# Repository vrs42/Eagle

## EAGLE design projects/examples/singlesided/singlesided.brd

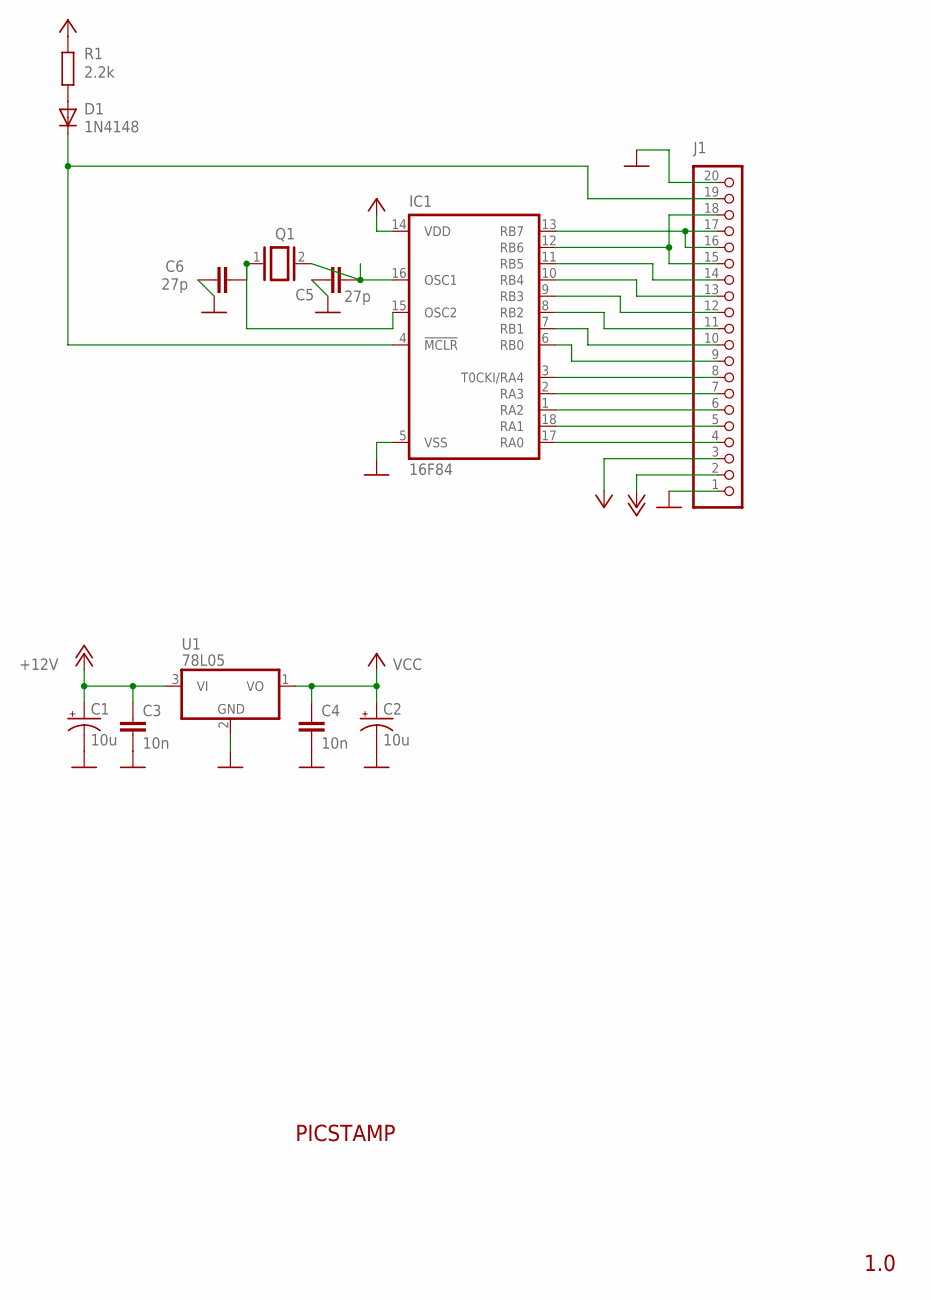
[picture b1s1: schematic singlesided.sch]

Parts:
C1, C2: 10u; E2,5-6
C3, C4: 10n; C025-025X050
C5, C6: 27p; C2.5-2
D1: 1N4148; DO35-10
IC1: 16F84; DIL18
J1: PINHD-1X20; 1X20
Q1: XTAL/S; QS
R1: 2.2k; 0207/10
U1: 78L05; TO92

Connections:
+12V: C1.+, C3.1, J1.2, U1.3 (VI)
A0: IC1.17 (RA0), J1.4
A1: IC1.18 (RA1), J1.5
A2: IC1.1 (RA2), J1.6
A3: IC1.2 (RA3), J1.7
A4: IC1.3 (T0CKI/RA4), J1.8
B0: IC1.6 (RB0), J1.9
B1: IC1.7 (RB1), J1.10
B2: IC1.8 (RB2), J1.11
B3: IC1.9 (RB3), J1.12
B4: IC1.10 (RB4), J1.13
B5: IC1.11 (RB5), J1.14
B6: IC1.12 (RB6), J1.15, J1.18
B7: IC1.13 (RB7), J1.16, J1.17
GND: C1.-, C2.-, C3.2, C4.2, C5.1, C6.1, IC1.5 (VSS), J1.1, J1.20, U1.2 (GND)
unnamed: D1.C, IC1.4 (!MCLR), J1.19
unnamed: D1.A, R1.1
unnamed: C5.2, IC1.16 (OSC1), Q1.2
unnamed: C6.2, IC1.15 (OSC2), Q1.1
VCC: C2.+, C4.1, IC1.14 (VDD), J1.3, R1.2, U1.1 (VO)

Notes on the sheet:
PICSTAMP
1.0

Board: 2 copper layers, 12 parts (0 on the bottom side), 20 nets, no tracks yet.

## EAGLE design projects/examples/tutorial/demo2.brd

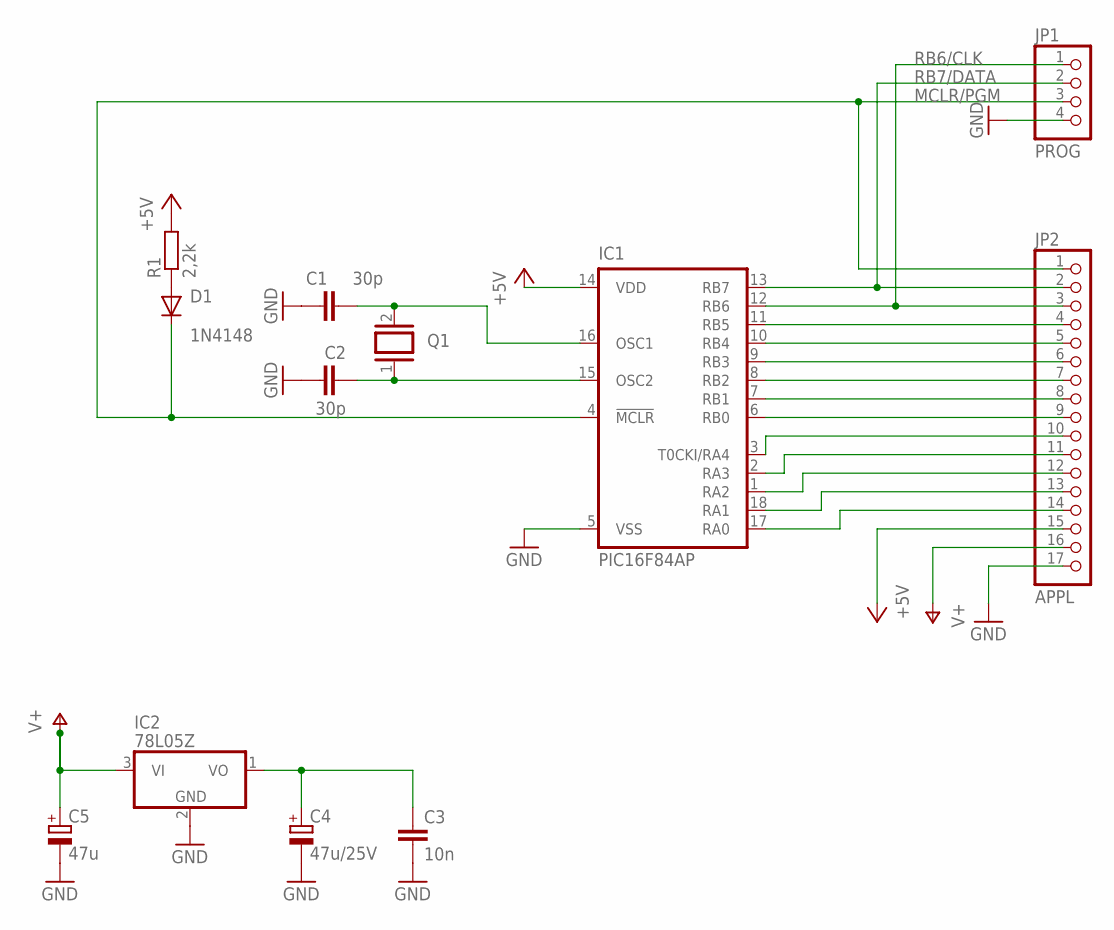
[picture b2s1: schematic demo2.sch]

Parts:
C1, C2: 30p; C1206
C3: 10n; C025-025X050
C4: 47u/25V; TAP5-45
C5: 47u; TAP5-45
D1: 1N4148; DO35-10
IC1: PIC16F84AP; DIL18
IC2: 78L05Z; TO92
JP1: PROG; 1X04
JP2: APPL; 1X17
Q1: XTAL/S; QS
R1: 2,2k; R1206

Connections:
+5V: IC1.14 (VDD), JP2.15, R1.2
GND: C1.1, C2.1, C3.2, C4.-, C5.-, IC1.5 (VSS), IC2.2 (GND), JP1.4, JP2.17
MCLR/PGM: D1.C, IC1.4 (!MCLR), JP1.3, JP2.1
unnamed: C3.1, C4.+, IC2.1 (VO)
unnamed: C1.2, IC1.16 (OSC1), Q1.2
unnamed: C2.2, IC1.15 (OSC2), Q1.1
unnamed: D1.A, R1.1
RA0: IC1.17 (RA0), JP2.14
RA1: IC1.18 (RA1), JP2.13
RA2: IC1.1 (RA2), JP2.12
RA3: IC1.2 (RA3), JP2.11
RA4: IC1.3 (T0CKI/RA4), JP2.10
RB0: IC1.6 (RB0), JP2.9
RB1: IC1.7 (RB1), JP2.8
RB2: IC1.8 (RB2), JP2.7
RB3: IC1.9 (RB3), JP2.6
RB4: IC1.10 (RB4), JP2.5
RB5: IC1.11 (RB5), JP2.4
RB6/CLK: IC1.12 (RB6), JP1.1, JP2.3
RB7/DATA: IC1.13 (RB7), JP1.2, JP2.2
V+: C5.+, IC2.3 (VI), JP2.16

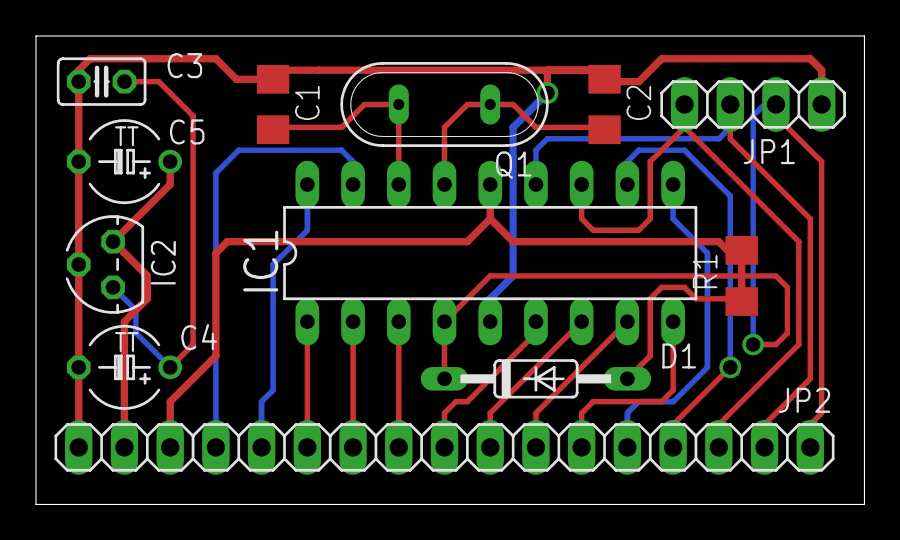
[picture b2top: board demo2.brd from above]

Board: 2 copper layers, 46.0 x 26.0 mm, 12 parts (0 on the bottom side), 21 nets.

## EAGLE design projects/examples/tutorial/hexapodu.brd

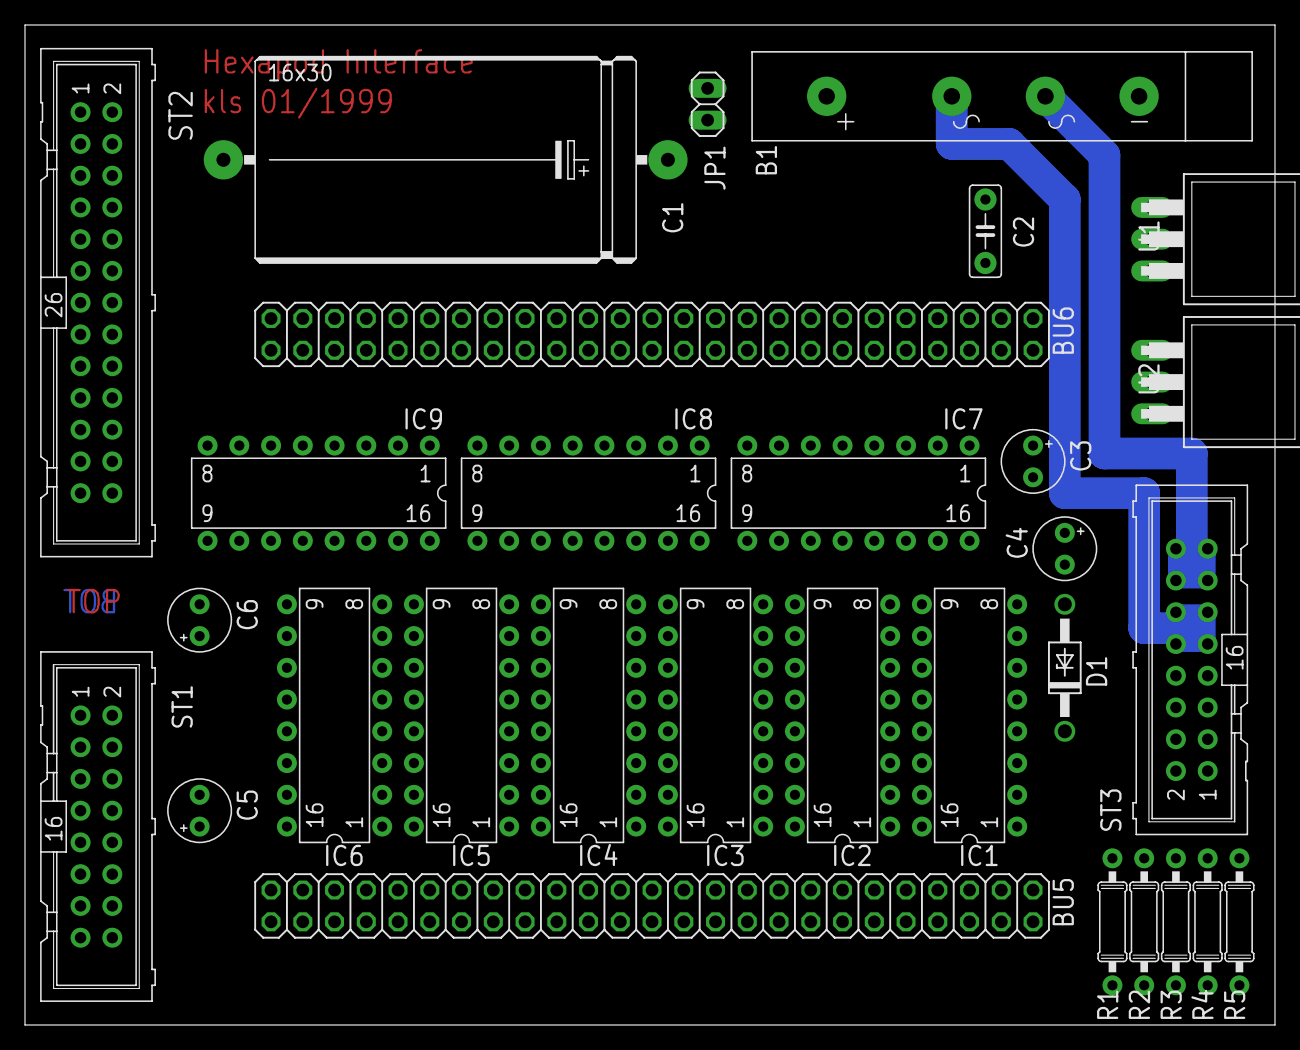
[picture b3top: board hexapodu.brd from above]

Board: 2 copper layers, 100.0 x 80.0 mm, 30 parts (0 on the bottom side), 68 nets.

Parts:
B1: FB100
BU5, BU6: PINHD-2X25; 2X25
C1: 2200uF/35V; E35-16
C2: 100nf; C5B2,5A
C3, C6: 4,7uf/35V; E2,5-5
C4, C5: 4,7uf/10V; E2,5-5
D1: BZX85; DO41Z10
IC1, IC2, IC3, IC4, IC5, IC6: HCTL2016; DIL-16
IC7, IC8, IC9: DS3668; DIL-16
JP1: PINHD-1X2; 1X02
R1, R2, R4, R5: 0207/10
R3: 10k; 0207/10@1
ST1, ST3: PINHD-2X8; ML16
ST2: PINHD-2X13; ML26
U1: 78S24; TO220H
U2: 7805; TO220H

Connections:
!OE0: BU6.5, IC1.4
!OE1: BU6.8, IC2.4
!OE2: BU6.7, IC3.4
!OE3: BU6.10, IC4.4
!OE4: BU6.9, IC5.4
!OE5: BU6.12, IC6.4
!RST: BU6.14, IC1.5, IC2.5, IC3.5, IC4.5, IC5.5, IC6.5
+5V: BU6.50, C4.+, C5.+, D1.C, IC1.16, IC2.16, IC3.16, IC4.16, IC5.16, IC6.16, IC7.11, IC8.11, IC9.11, R1.1, R2.1, R4.1, ST1.3, ST1.4, U2.3
+24V: C3.+, C6.+, IC7.2, IC7.7, IC8.2, IC8.7, IC9.2, IC9.7, R5.1, ST2.1, ST2.3, ST2.5, ST2.7, ST2.9, ST2.11, ST2.13, ST2.15, ST2.17, ST2.19, ST2.21, ST2.23, ST2.25, ST2.26, U1.3
AC1: B1.AC1, ST3.9, ST3.10, ST3.11, ST3.12
AC2: B1.AC2, ST3.13, ST3.14, ST3.15, ST3.16
CLK: BU6.1, IC1.2, IC2.2, IC3.2, IC4.2, IC5.2, IC6.2
COIL0: IC7.1, ST2.2
COIL1: IC7.3, ST2.4
COIL2: IC7.6, ST2.6
COIL3: IC7.8, ST2.8
COIL4: IC8.1, ST2.10
COIL5: IC8.3, ST2.12
COIL6: IC8.6, ST2.14
COIL7: IC8.8, ST2.16
COIL8: IC9.1, ST2.18
COIL9: IC9.3, ST2.20
COIL10: IC9.6, ST2.22
COIL11: IC9.8, ST2.24
D0: BU6.13, IC1.1, IC2.1, IC3.1, IC4.1, IC5.1, IC6.1
D1: BU6.16, IC1.15, IC2.15, IC3.15, IC4.15, IC5.15, IC6.15
D2: BU6.15, IC1.14, IC2.14, IC3.14, IC4.14, IC5.14, IC6.14
D3: BU6.18, IC1.13, IC2.13, IC3.13, IC4.13, IC5.13, IC6.13
D4: BU6.17, IC1.12, IC2.12, IC3.12, IC4.12, IC5.12, IC6.12
D5: BU6.20, IC1.11, IC2.11, IC3.11, IC4.11, IC5.11, IC6.11
D6: BU6.19, IC1.10, IC2.10, IC3.10, IC4.10, IC5.10, IC6.10
D7: BU6.22, IC1.9, IC2.9, IC3.9, IC4.9, IC5.9, IC6.9
EN: BU5.9, IC7.14, IC8.14, IC9.14, R3.2
ENC0: IC1.7, ST1.5
ENC1: IC1.6, ST1.6
ENC2: IC2.7, ST1.7
ENC3: IC2.6, ST1.8
ENC4: IC3.7, ST1.9
ENC5: IC3.6, ST1.10
ENC6: IC4.7, ST1.11
ENC7: IC4.6, ST1.12
ENC8: IC5.7, ST1.13
ENC9: IC5.6, ST1.14
ENC10: IC6.7, ST1.15
ENC11: IC6.6, ST1.16
GND: B1.-, BU6.49, C1.-, C2.1, C3.-, C4.-, C5.-, C6.-, D1.A, IC1.8, IC2.8, IC3.8, IC4.8, IC5.8, IC6.8, IC7.4, IC7.5, IC7.12, IC7.13, IC8.4, IC8.5, IC8.12, IC8.13, IC9.4, IC9.5, IC9.12, IC9.13, R3.1, ST1.1, ST1.2, ST3.2, ST3.4, U1.2, U2.2
unnamed: R5.2, ST3.1
unnamed: R4.2, ST3.3
unnamed: R2.2, ST3.5
unnamed: R1.2, ST3.7
unnamed: BU6.35, JP1.2
unnamed: BU6.37, JP1.1
SEL: BU6.11, IC1.3, IC2.3, IC3.3, IC4.3, IC5.3, IC6.3
STATUS0: BU5.7, ST3.8
STATUS1: BU5.6, ST3.6
VALVE0: BU5.21, IC7.16
VALVE1: BU5.20, IC7.15
VALVE2: BU5.19, IC7.10
VALVE3: BU5.18, IC7.9
VALVE4: BU5.17, IC8.16
VALVE5: BU5.16, IC8.15
VALVE6: BU5.15, IC8.10
VALVE7: BU5.14, IC8.9
VALVE8: BU5.13, IC9.16
VALVE9: BU5.12, IC9.15
VALVE10: BU5.11, IC9.10
VALVE11: BU5.10, IC9.9
VIN: B1.+, C1.+, C2.2, U1.1, U2.1

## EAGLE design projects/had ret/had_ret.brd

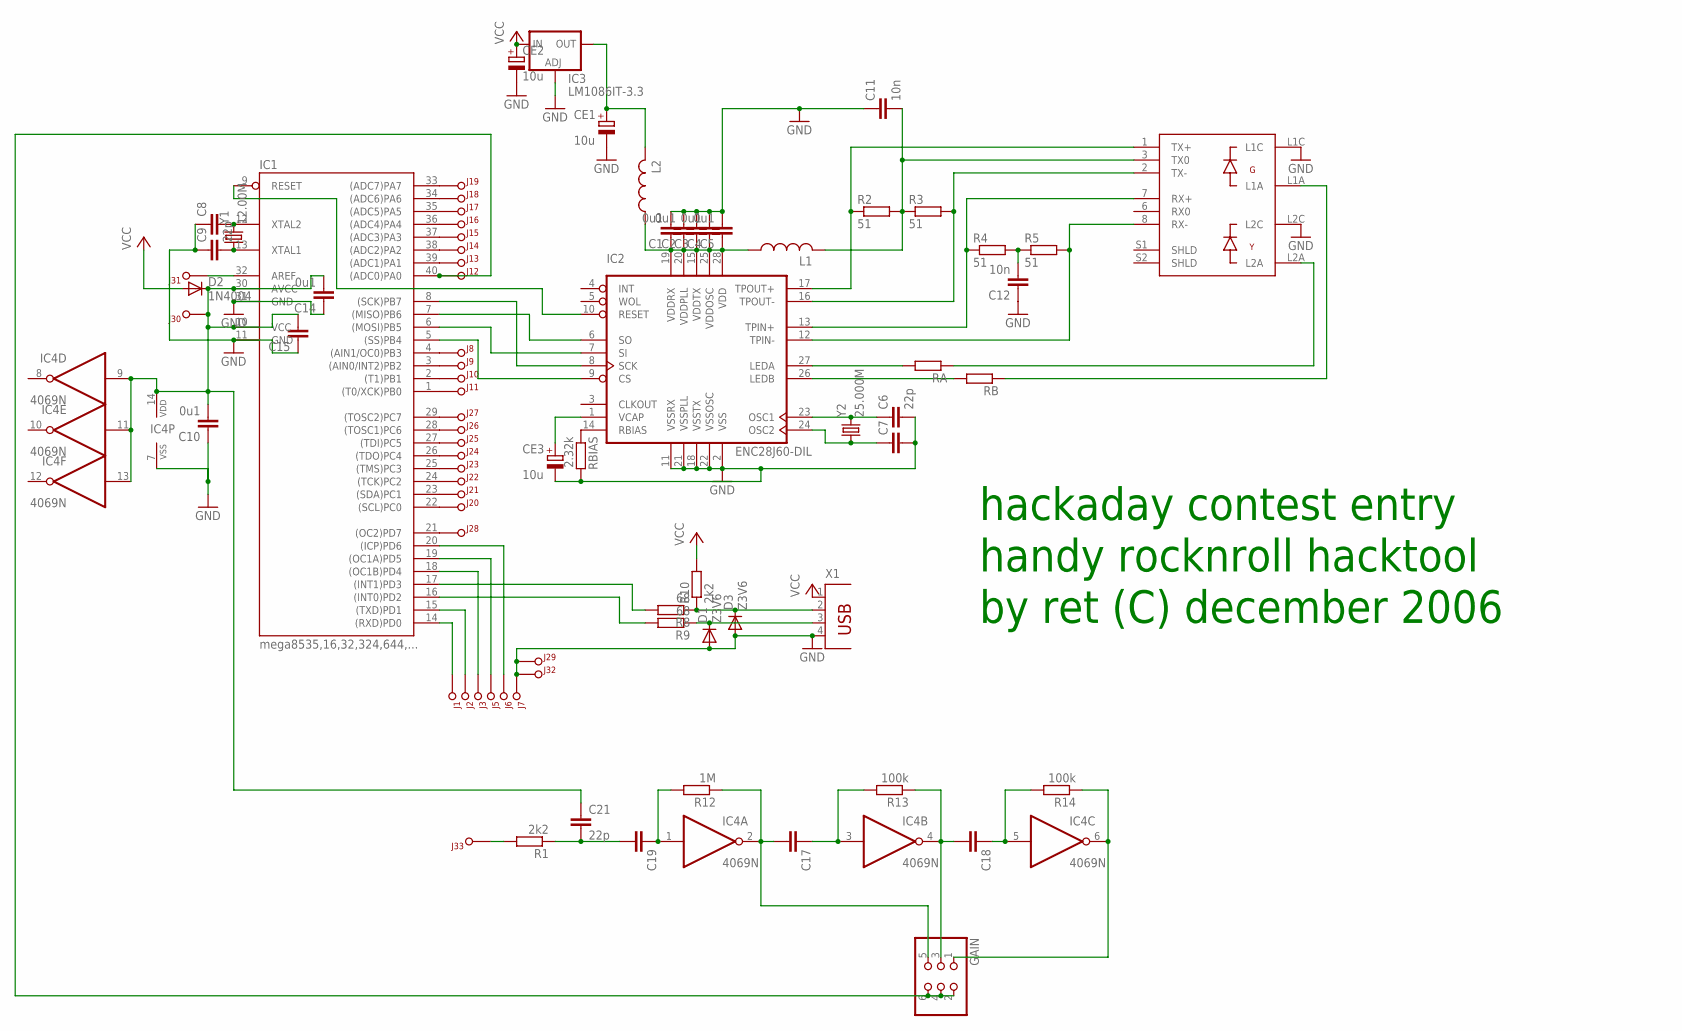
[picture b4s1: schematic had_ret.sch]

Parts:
C1, C2, C4, C5, C10, C14: 0u1; 0805
C3, C7, C8, C15, C17, C18, C19: C0805; 0805
C6, C9, C21: 22p; 0805
C11, C12: 10n; 0805
CE1, CE2, CE3: 10u; CT3528
D1, D3: Z3V6; DIODE
D2: 1N4004; DO41-10
GAIN: PINHD-2X3; 2X03
IC1: mega8535,16,32,324,644,...; DIL40
IC2: ENC28J60-DIL; DIL28-3
IC3: LM1086IT-3.3; 317TS
IC4: 4069N; DIL14
J1, J2, J3, J5, J6, J7, J8, J9, J10, J11, J12, J13, J14, J15, J16, J17, J18, J19, J20, J21, J22, J23, J24, J25, J26, J27, J28, J29, J30, J31, J32, J33: PINMA01; MA01-1PIN
J4: 8P8C-TRAF
L1, L2: L0805; 0805
R1, R10: 2k2; 0805
R2, R3, R4, R5: 51; 0805
R8, R9: 68; 0805
R12: 1M; 0805
R13, R14: 100k; 0805
RA: R-EU_0204/5; 0204/5
RB: R-EU_0204/5; 0204/5
RBIAS: 2.32k; 0204/7
X1: PN61729
Y1: 12.00M; HC49/S
Y2: 25.000M; HC49/S

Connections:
+3V3: CE1.+, IC3.2 (OUT), L2.2
GND: C1.2, C2.2, C3.2, C4.2, C5.2, C6.2, C7.2, C8.1, C9.1, C10.1, C11.1, C12.1, C14.1, C15.1, CE1.-, CE2.-, CE3.-, D1.A, D3.A, IC1.11 (GND), IC1.31 (GND), IC2.2 (VSS), IC2.11 (VSSRX), IC2.18 (VSSTX), IC2.21 (VSSPLL), IC2.22 (VSSOSC), IC3.1 (ADJ), IC4.7 (VSS), J4.L1C, J4.L2C, J7.1, J29.1, J32.1, RBIAS.2, X1.4
MISO: IC1.7 ((MISO)PB6), IC2.6 (SO)
MOSI: IC1.6 ((MOSI)PB5), IC2.7 (SI)
unnamed: IC1.15 ((TXD)PD1), J2.1
unnamed: IC1.14 ((RXD)PD0), J1.1
unnamed: CE3.+, IC2.1 (VCAP)
unnamed: IC1.17 ((INT1)PD3), R8.2
unnamed: IC1.16 ((INT0)PD2), R9.2
unnamed: C1.1, C2.1, C3.1, C4.1, C5.1, IC2.15 (VDDTX), IC2.19 (VDDRX), IC2.20 (VDDPLL), IC2.25 (VDDOSC), IC2.28 (VDD), L1.1, L2.1
unnamed: IC1.32 (AREF), J31.1
unnamed: IC2.26 (LEDB), RB.2
unnamed: IC2.27 (LEDA), RA.2
unnamed: IC1.18 ((OC1B)PD4), J3.1
unnamed: J4.L2A, RA.1
unnamed: IC2.16 (TPOUT-), J4.2 (TX-), R3.2
unnamed: IC2.12 (TPIN-), J4.8 (RX-), R5.2
unnamed: IC2.13 (TPIN+), J4.7 (RX+), R4.1
unnamed: C11.2, J4.3 (TX0), L1.2, R2.2, R3.1
unnamed: C8.2, IC1.12 (XTAL2), Y1.2
unnamed: C9.2, IC1.13 (XTAL1), Y1.1
unnamed: C6.1, IC2.23 (OSC1), Y2.2
unnamed: C7.1, IC2.24 (OSC2), Y2.1
unnamed: IC2.17 (TPOUT+), J4.1 (TX+), R2.1
unnamed: J4.L1A, RB.1
unnamed: IC2.14 (RBIAS), RBIAS.1
unnamed: IC1.19 ((OC1A)PD5), J5.1
unnamed: IC1.20 ((ICP)PD6), J6.1
unnamed: D3.K (C), R8.1, R10.1, X1.2
unnamed: D1.K (C), R9.1, X1.3
unnamed: IC1.4 ((AIN1/OC0)PB3), J8.1
unnamed: IC1.3 ((AIN0/INT2)PB2), J9.1
unnamed: IC1.2 ((T1)PB1), J10.1
unnamed: IC1.1 ((T0/XCK)PB0), J11.1
unnamed: GAIN.2, GAIN.4, GAIN.6, IC1.40 ((ADC0)PA0), J12.1
unnamed: IC1.39 ((ADC1)PA1), J13.1
unnamed: IC1.38 ((ADC2)PA2), J14.1
unnamed: IC1.37 ((ADC3)PA3), J15.1
unnamed: IC1.36 ((ADC4)PA4), J16.1
unnamed: IC1.35 ((ADC5)PA5), J17.1
unnamed: IC1.34 ((ADC6)PA6), J18.1
unnamed: IC1.33 ((ADC7)PA7), J19.1
unnamed: IC1.22 ((SCL)PC0), J20.1
unnamed: IC1.23 ((SDA)PC1), J21.1
unnamed: IC1.24 ((TCK)PC2), J22.1
unnamed: IC1.25 ((TMS)PC3), J23.1
unnamed: IC1.26 ((TDO)PC4), J24.1
unnamed: IC1.27 ((TDI)PC5), J25.1
unnamed: IC1.28 ((TOSC1)PC6), J26.1
unnamed: IC1.29 ((TOSC2)PC7), J27.1
unnamed: IC1.21 ((OC2)PD7), J28.1
unnamed: C12.2, R4.2, R5.1
unnamed: C19.1, IC4.1 (I), R12.2
unnamed: C17.2, GAIN.5, IC4.2 (O), R12.1
unnamed: C17.1, IC4.3 (I), R13.2
unnamed: C18.2, GAIN.3, IC4.4 (O), R13.1
unnamed: J33.1, R1.2
unnamed: C19.2, C21.2, R1.1
unnamed: C18.1, IC4.5 (I), R14.2
unnamed: GAIN.1, IC4.6 (O), R14.1
RST: IC1.9 (RESET), IC2.10 (RESET)
SCK: IC1.8 ((SCK)PB7), IC2.8 (SCK)
SS: IC1.5 ((SS)PB4), IC2.9 (CS)
V4.4: C10.2, C14.2, C15.2, C21.1, D2.C, IC1.10 (VCC), IC1.30 (AVCC), IC4.9 (I), IC4.11 (I), IC4.13 (I), IC4.14 (VDD), J30.1
VCC: CE2.+, D2.A, IC3.3 (IN), R10.2, X1.1

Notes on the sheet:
hackaday contest entry
handy rocknroll hacktool
by ret (C) december 2006

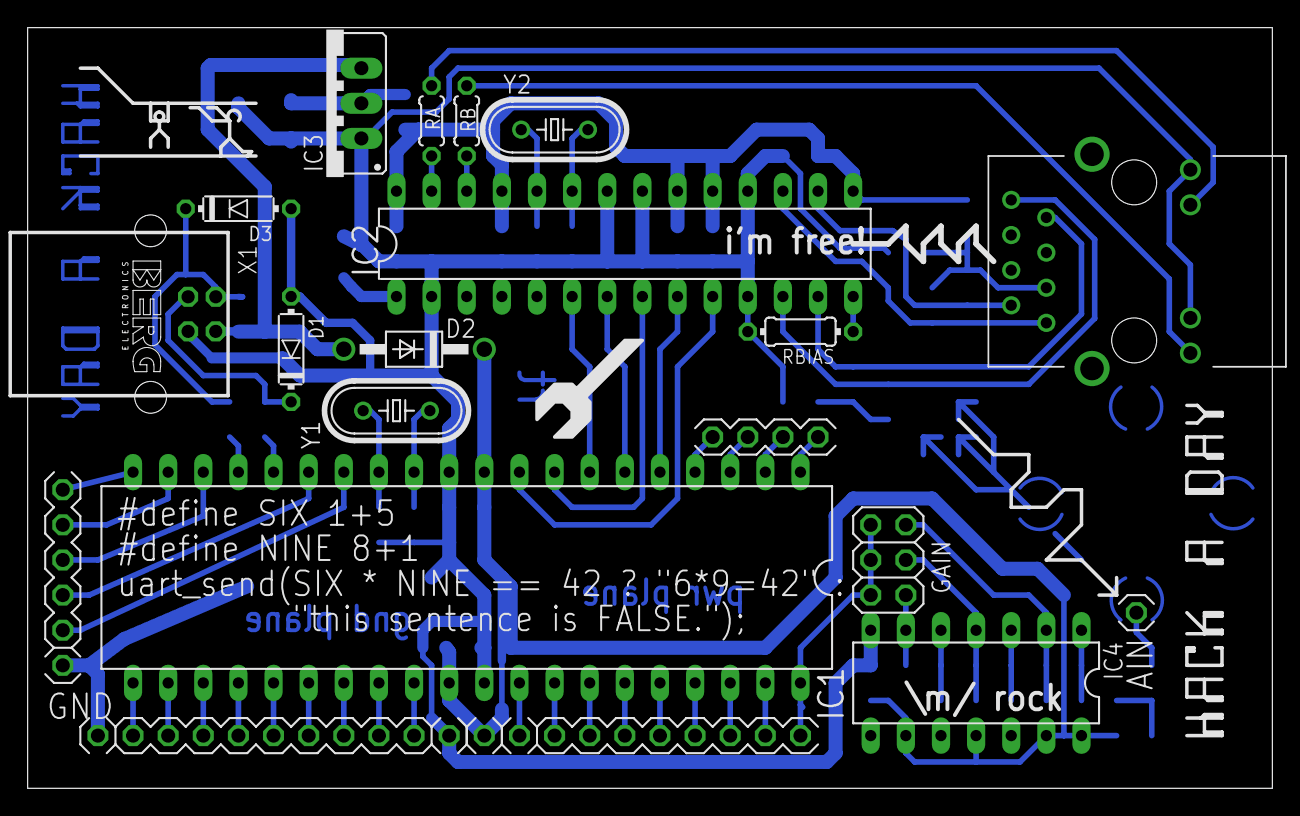
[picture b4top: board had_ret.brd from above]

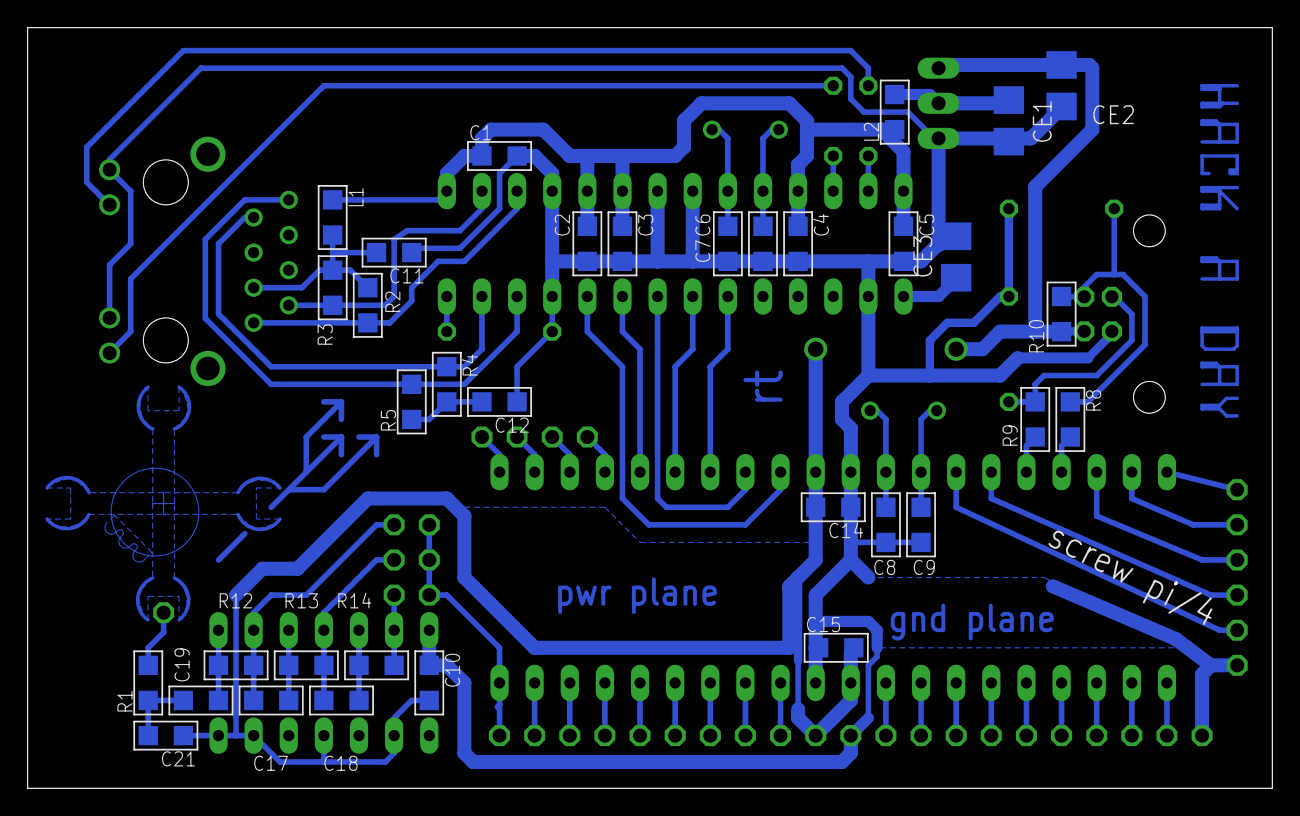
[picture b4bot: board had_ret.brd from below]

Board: 2 copper layers, 90.0 x 55.0 mm, 81 parts (34 on the bottom side), 65 nets.

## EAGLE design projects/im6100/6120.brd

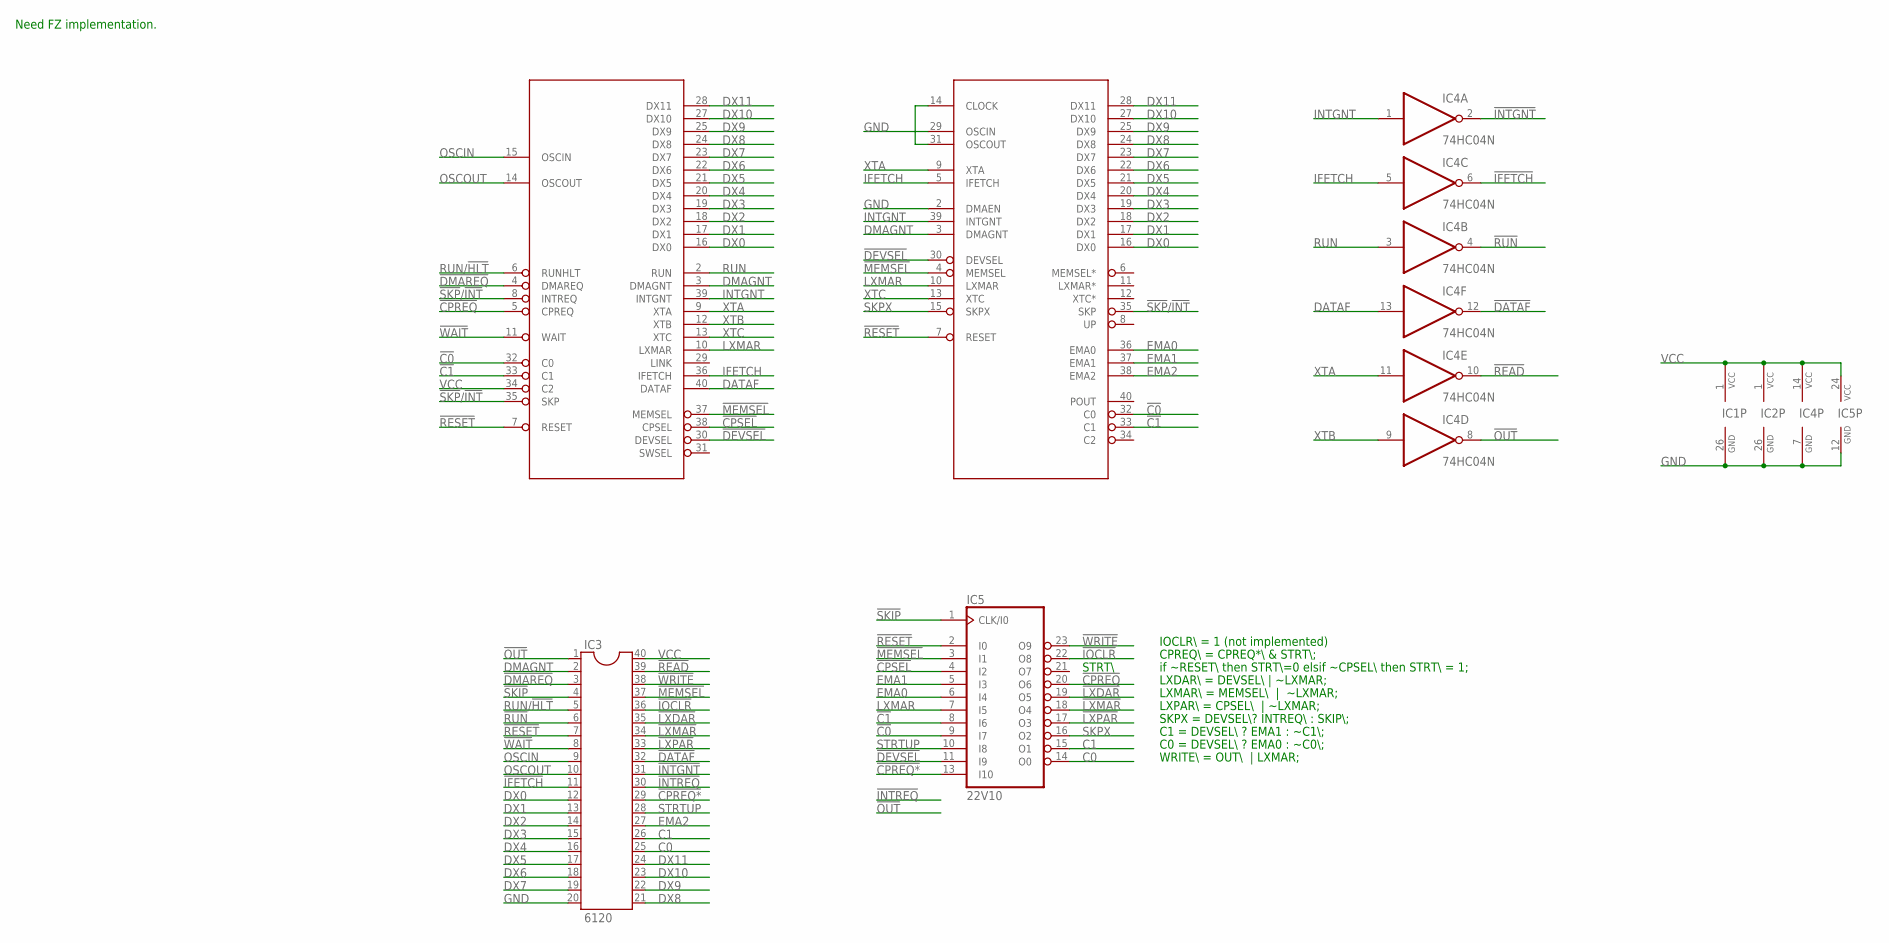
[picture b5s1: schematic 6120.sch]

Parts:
IC1: IM6100; DIL40
IC2: IM6102; DIL40
IC3: 6120; DIL40
IC4: 74HC04N; DIL14
IC5: 22V10; DIL24-3

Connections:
!C0: IC1.32 (C0), IC2.32 (C0), IC5.9 (I7)
!C1: IC1.33 (C1), IC2.33 (C1), IC5.8 (I6)
!CPREQ: IC1.5 (CPREQ), IC5.20 (O6)
!CPREQ*: IC3.29, IC5.13 (I10)
!CPSEL: IC1.38 (CPSEL), IC5.4 (I2)
!DATAF: IC3.32, IC4.12 (O)
!DEVSEL: IC1.30 (DEVSEL), IC2.30 (DEVSEL), IC5.11 (I9)
!DMAREQ: IC1.4 (DMAREQ), IC3.3
!IFETCH: IC3.11, IC4.6 (O)
!INTGNT: IC3.31, IC4.2 (O)
!INTREQ: IC3.30
!IOCLR: IC3.36, IC5.22 (O8)
!LXDAR: IC3.35, IC5.19 (O5)
!LXMAR: IC3.34, IC5.18 (O4)
!LXPAR: IC3.33, IC5.17 (O3)
!MEMSEL: IC1.37 (MEMSEL), IC2.4 (MEMSEL), IC3.37, IC5.3 (I1)
!OUT: IC3.1, IC4.8 (O)
!READ: IC3.39, IC4.10 (O)
!RESET: IC1.7 (RESET), IC2.7 (RESET), IC3.7, IC5.2 (I0)
!RUN: IC3.6, IC4.4 (O)
!SKIP: IC3.4, IC5.1 (CLK/I0)
!SKP!/!INT: IC1.8 (INTREQ), IC1.35 (SKP), IC2.35 (SKP)
!WAIT: IC1.11 (WAIT), IC3.8
!WRITE: IC3.38, IC5.23 (O9)
C0: IC3.25, IC5.14 (O0)
C1: IC3.26, IC5.15 (O1)
DATAF: IC1.40 (DATAF), IC4.13 (I)
DMAGNT: IC1.3 (DMAGNT), IC2.3 (DMAGNT), IC3.2
DX0: IC1.16 (DX0), IC2.16 (DX0), IC3.12
DX1: IC1.17 (DX1), IC2.17 (DX1), IC3.13
DX2: IC1.18 (DX2), IC2.18 (DX2), IC3.14
DX3: IC1.19 (DX3), IC2.19 (DX3), IC3.15
DX4: IC1.20 (DX4), IC2.20 (DX4), IC3.16
DX5: IC1.21 (DX5), IC2.21 (DX5), IC3.17
DX6: IC1.22 (DX6), IC2.22 (DX6), IC3.18
DX7: IC1.23 (DX7), IC2.23 (DX7), IC3.19
DX8: IC1.24 (DX8), IC2.24 (DX8), IC3.21
DX9: IC1.25 (DX9), IC2.25 (DX9), IC3.22
DX10: IC1.27 (DX10), IC2.27 (DX10), IC3.23
DX11: IC1.28 (DX11), IC2.28 (DX11), IC3.24
EMA0: IC2.36 (EMA0), IC5.6 (I4)
EMA1: IC2.37 (EMA1), IC5.5 (I3)
EMA2: IC2.38 (EMA2), IC3.27
GND: IC1.26 (GND), IC2.2 (DMAEN), IC2.26 (GND), IC2.29 (OSCIN), IC3.20, IC4.7 (GND), IC5.12 (GND)
IFETCH: IC1.36 (IFETCH), IC2.5 (IFETCH), IC4.5 (I)
INTGNT: IC1.39 (INTGNT), IC2.39 (INTGNT), IC4.1 (I)
LXMAR: IC1.10 (LXMAR), IC2.10 (LXMAR), IC5.7 (I5)
unnamed: IC2.14 (CLOCK), IC2.31 (OSCOUT)
OSCIN: IC1.15 (OSCIN), IC3.9
OSCOUT: IC1.14 (OSCOUT), IC3.10
RUN: IC1.2 (RUN), IC4.3 (I)
RUN/!HLT: IC1.6 (RUNHLT), IC3.5
SKPX: IC2.15 (SKPX), IC5.16 (O2)
STRTUP: IC3.28, IC5.10 (I8)
VCC: IC1.1 (VCC), IC1.34 (C2), IC2.1 (VCC), IC3.40, IC4.14 (VCC), IC5.24 (VCC)
XTA: IC1.9 (XTA), IC2.9 (XTA), IC4.11 (I)
XTB: IC1.12 (XTB), IC4.9 (I)
XTC: IC1.13 (XTC), IC2.13 (XTC)

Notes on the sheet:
Need FZ implementation.
C0 = DEVSEL\\ ? EMA0 : ~C0\\;
C1 = DEVSEL\\ ? EMA1 : ~C1\\;
LXPAR\\ = CPSEL\\ | ~LXMAR;
LXMAR\\ = MEMSEL\\ | ~LXMAR;
CPREQ\\ = CPREQ*\\ & STRT\\;
LXDAR\\ = DEVSEL\\ | ~LXMAR;
SKPX = DEVSEL\\? INTREQ\\ : SKIP\\;
WRITE\\ = OUT\\ | LXMAR;
IOCLR\\ = 1 (not implemented)
if ~RESET\\ then STRT\\=0 elsif ~CPSEL\\ then STRT\\ = 1;
STRT\\

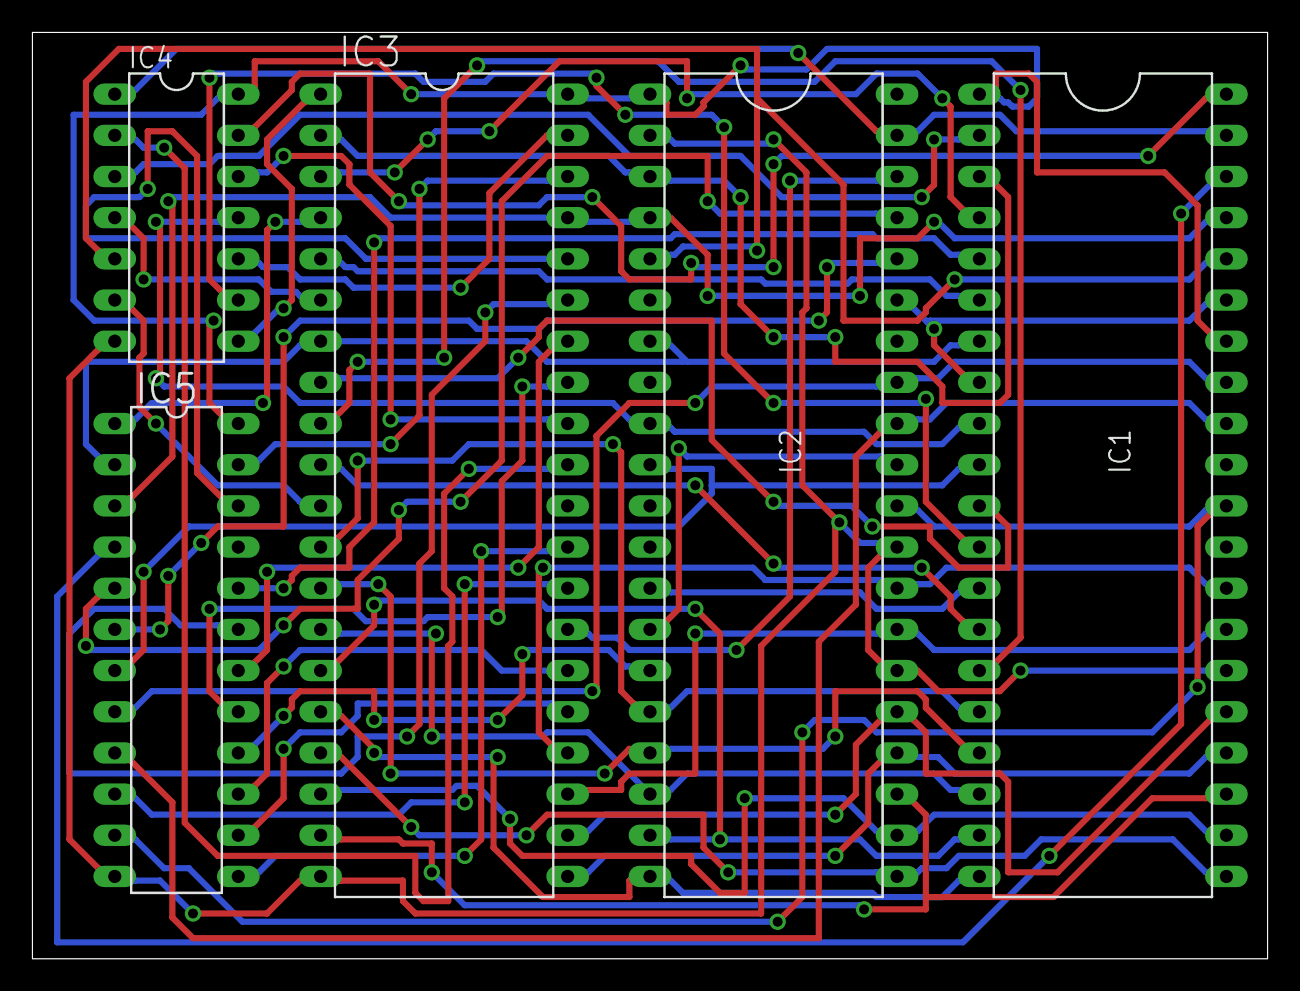
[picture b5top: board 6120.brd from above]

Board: 2 copper layers, 76.2 x 57.1 mm, 5 parts (0 on the bottom side), 57 nets.

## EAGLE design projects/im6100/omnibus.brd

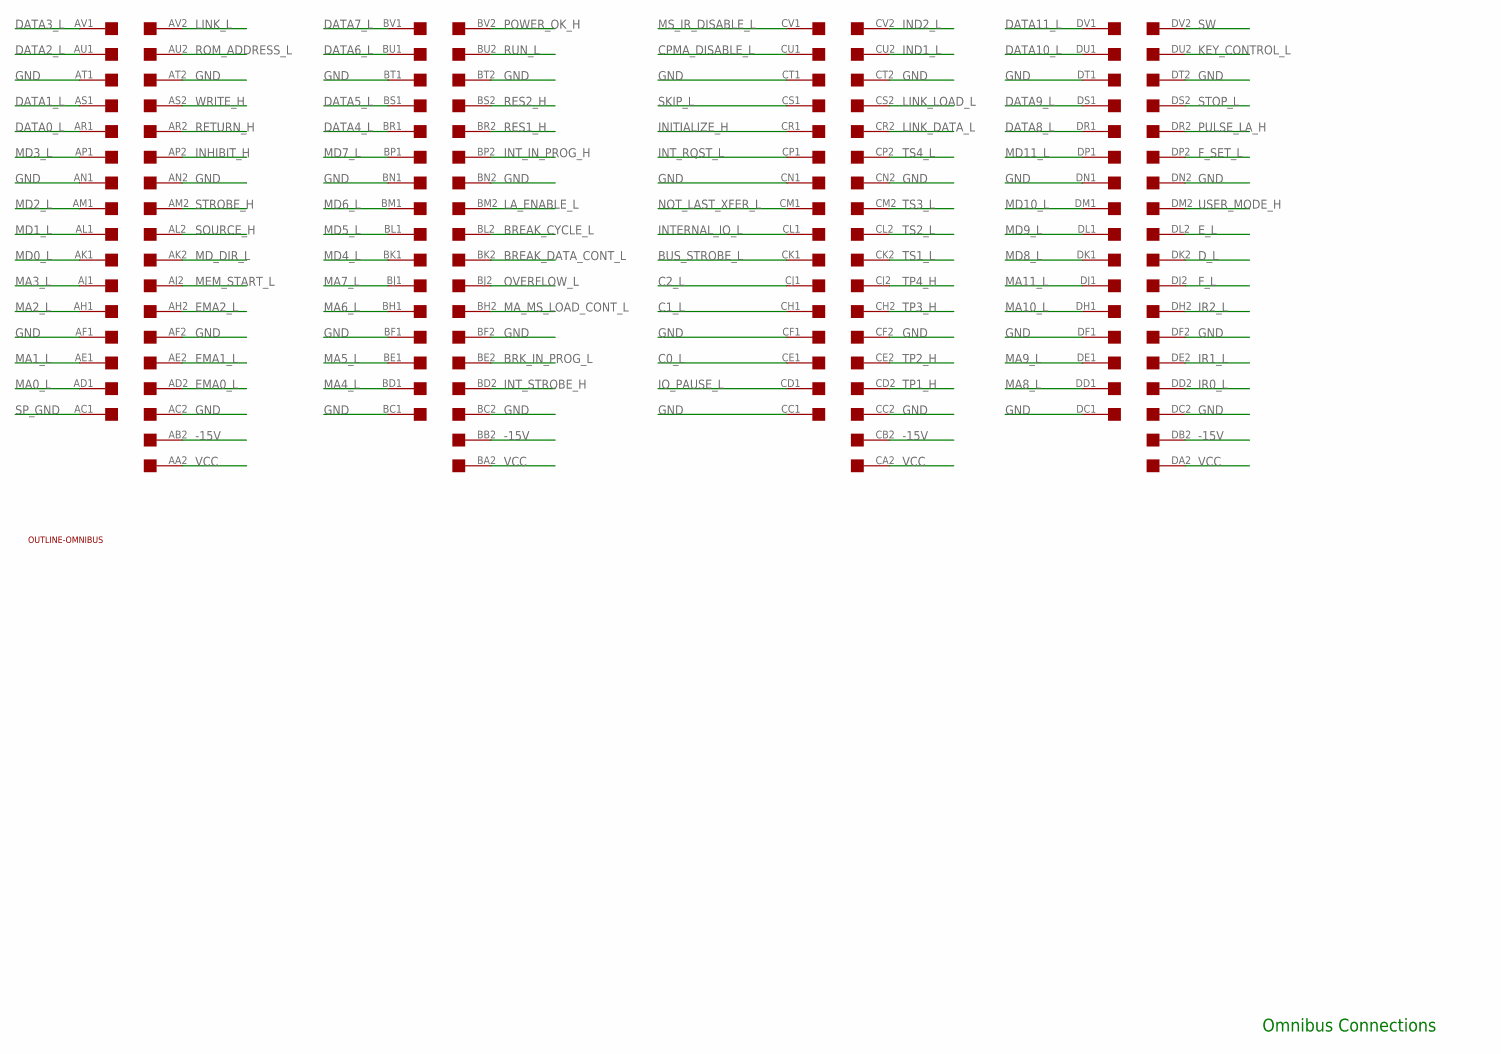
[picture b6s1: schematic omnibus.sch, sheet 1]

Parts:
U$1: OUTLINE-OMNIBUS; OMNIBUS
U$2: QUAD; EDGE-CON8

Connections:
-15V: U$2.AB2, U$2.BB2, U$2.CB2, U$2.DB2
BREAK_CYCLE_L: U$2.BL2
BREAK_DATA_CONT_L: U$2.BK2
BRK_IN_PROG_L: U$2.BE2
BUS_STROBE_L: U$2.CK1
C0_L: U$2.CE1; also elsewhere on the board
C1_L: U$2.CH1; also elsewhere on the board
C2_L: U$2.CJ1
CPMA_DISABLE_L: U$2.CU1
DATA0_L: U$2.AR1; also elsewhere on the board
DATA1_L: U$2.AS1; also elsewhere on the board
DATA2_L: U$2.AU1; also elsewhere on the board
DATA3_L: U$2.AV1; also elsewhere on the board
DATA4_L: U$2.BR1; also elsewhere on the board
DATA5_L: U$2.BS1; also elsewhere on the board
DATA6_L: U$2.BU1; also elsewhere on the board
DATA7_L: U$2.BV1; also elsewhere on the board
DATA8_L: U$2.DR1; also elsewhere on the board
DATA9_L: U$2.DS1; also elsewhere on the board
DATA10_L: U$2.DU1; also elsewhere on the board
DATA11_L: U$2.DV1; also elsewhere on the board
D_L: U$2.DK2
EMA0_L: U$2.AD2; also elsewhere on the board
EMA1_L: U$2.AE2; also elsewhere on the board
EMA2_L: U$2.AH2; also elsewhere on the board
E_L: U$2.DL2
F_L: U$2.DJ2
F_SET_L: U$2.DP2
GND: U$2.AC2, U$2.AF1, U$2.AF2, U$2.AN1, U$2.AN2, U$2.AT1, U$2.AT2, U$2.BC1, U$2.BC2, U$2.BF1, U$2.BF2, U$2.BN1, U$2.BN2, U$2.BT1, U$2.BT2, U$2.CC1, U$2.CC2, U$2.CF1, U$2.CF2, U$2.CN1, U$2.CN2, U$2.CT1, U$2.CT2, U$2.DC1, U$2.DC2, U$2.DF1, U$2.DF2, U$2.DN1, U$2.DN2, U$2.DT1, U$2.DT2; also elsewhere on the board
IND1_L: U$2.CU2
IND2_L: U$2.CV2
INHIBIT_H: U$2.AP2
INITIALIZE_H: U$2.CR1
INTERNAL_IO_L: U$2.CL1
INT_IN_PROG_H: U$2.BP2
INT_RQST_L: U$2.CP1; also elsewhere on the board
INT_STROBE_H: U$2.BD2
IO_PAUSE_L: U$2.CD1; also elsewhere on the board
IR0_L: U$2.DD2
IR1_L: U$2.DE2
IR2_L: U$2.DH2
KEY_CONTROL_L: U$2.DU2
LA_ENABLE_L: U$2.BM2
LINK_DATA_L: U$2.CR2
LINK_L: U$2.AV2
LINK_LOAD_L: U$2.CS2
MA0_L: U$2.AD1
MA1_L: U$2.AE1
MA2_L: U$2.AH1
MA3_L: U$2.AJ1
MA4_L: U$2.BD1
MA5_L: U$2.BE1
MA6_L: U$2.BH1
MA7_L: U$2.BJ1
MA8_L: U$2.DD1
MA9_L: U$2.DE1
MA10_L: U$2.DH1
MA11_L: U$2.DJ1
MA_MS_LOAD_CONT_L: U$2.BH2
MD0_L: U$2.AK1; also elsewhere on the board
MD1_L: U$2.AL1; also elsewhere on the board
MD2_L: U$2.AM1; also elsewhere on the board
MD3_L: U$2.AP1; also elsewhere on the board
MD4_L: U$2.BK1; also elsewhere on the board
MD5_L: U$2.BL1; also elsewhere on the board
MD6_L: U$2.BM1; also elsewhere on the board
MD7_L: U$2.BP1; also elsewhere on the board
MD8_L: U$2.DK1; also elsewhere on the board
MD9_L: U$2.DL1; also elsewhere on the board
MD10_L: U$2.DM1; also elsewhere on the board
MD11_L: U$2.DP1; also elsewhere on the board
MD_DIR_L: U$2.AK2
MEM_START_L: U$2.AJ2
MS_IR_DISABLE_L: U$2.CV1
NOT_LAST_XFER_L: U$2.CM1
OVERFLOW_L: U$2.BJ2
POWER_OK_H: U$2.BV2
PULSE_LA_H: U$2.DR2
RES1_H: U$2.BR2
RES2_H: U$2.BS2
RETURN_H: U$2.AR2
ROM_ADDRESS_L: U$2.AU2
RUN_L: U$2.BU2
SKIP_L: U$2.CS1; also elsewhere on the board
SOURCE_H: U$2.AL2
SP_GND: U$2.AC1
STOP_L: U$2.DS2
STROBE_H: U$2.AM2
SW: U$2.DV2
TP1_H: U$2.CD2
TP2_H: U$2.CE2
TP3_H: U$2.CH2; also elsewhere on the board
TP4_H: U$2.CJ2
TS1_L: U$2.CK2
TS2_L: U$2.CL2
TS3_L: U$2.CM2
TS4_L: U$2.CP2
USER_MODE_H: U$2.DM2
VCC: U$2.AA2, U$2.BA2, U$2.CA2, U$2.DA2; also elsewhere on the board
WRITE_H: U$2.AS2

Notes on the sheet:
Omnibus Connections
